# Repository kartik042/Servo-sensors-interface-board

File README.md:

This interface board uses Arduino board to control servo motors and has the following features:
1. Read data from airflow sensors
2. Uses 12VDC input
3. Has a TFT screen to display sensor values and UI elements to control the motors.
4. LDO voltage regulator MIC2940A to convert 12VDC to 3.3VDC
5. TMUX1208PWR multiplexer for data and clock signals
6. Pressure sensor that measures static pressure and the data is available on the display

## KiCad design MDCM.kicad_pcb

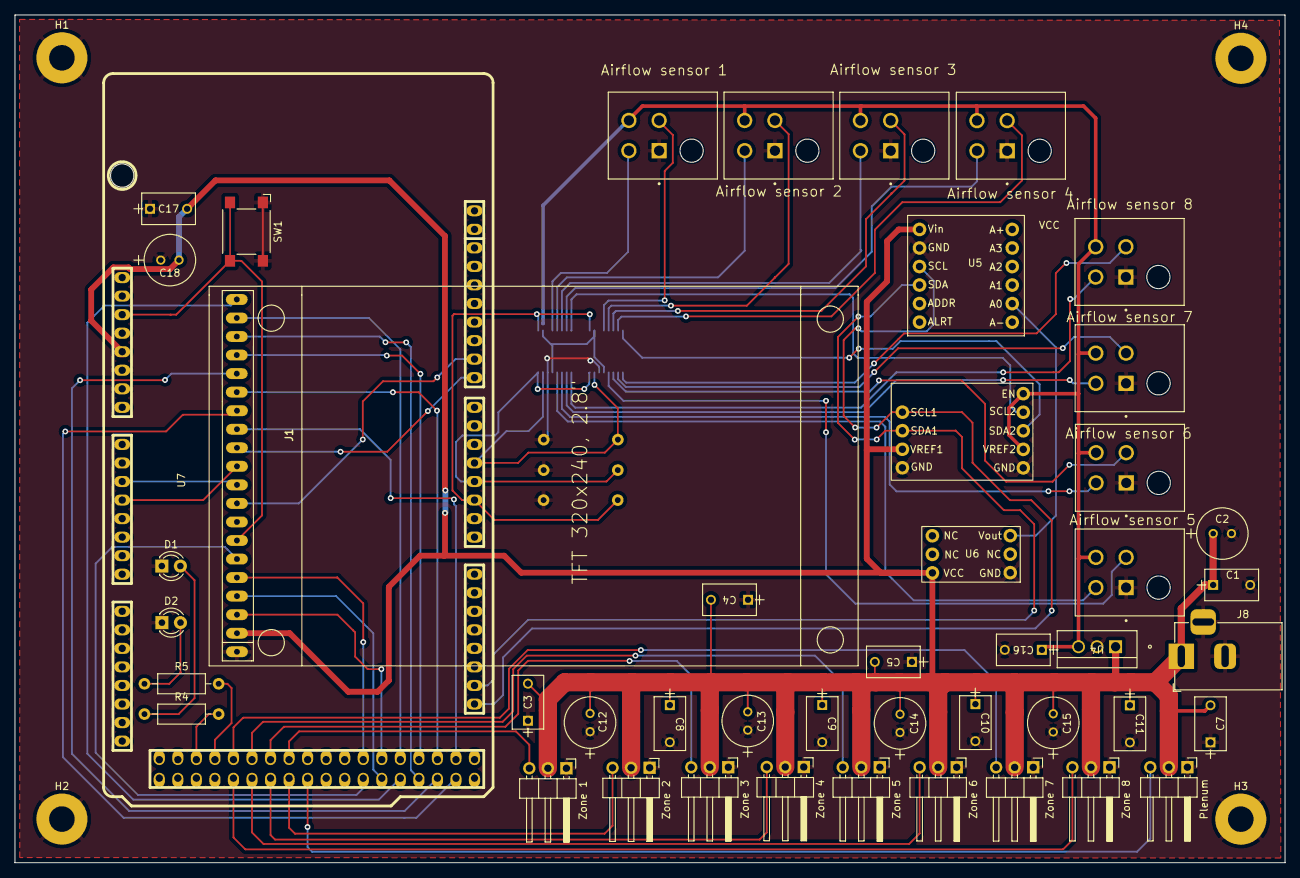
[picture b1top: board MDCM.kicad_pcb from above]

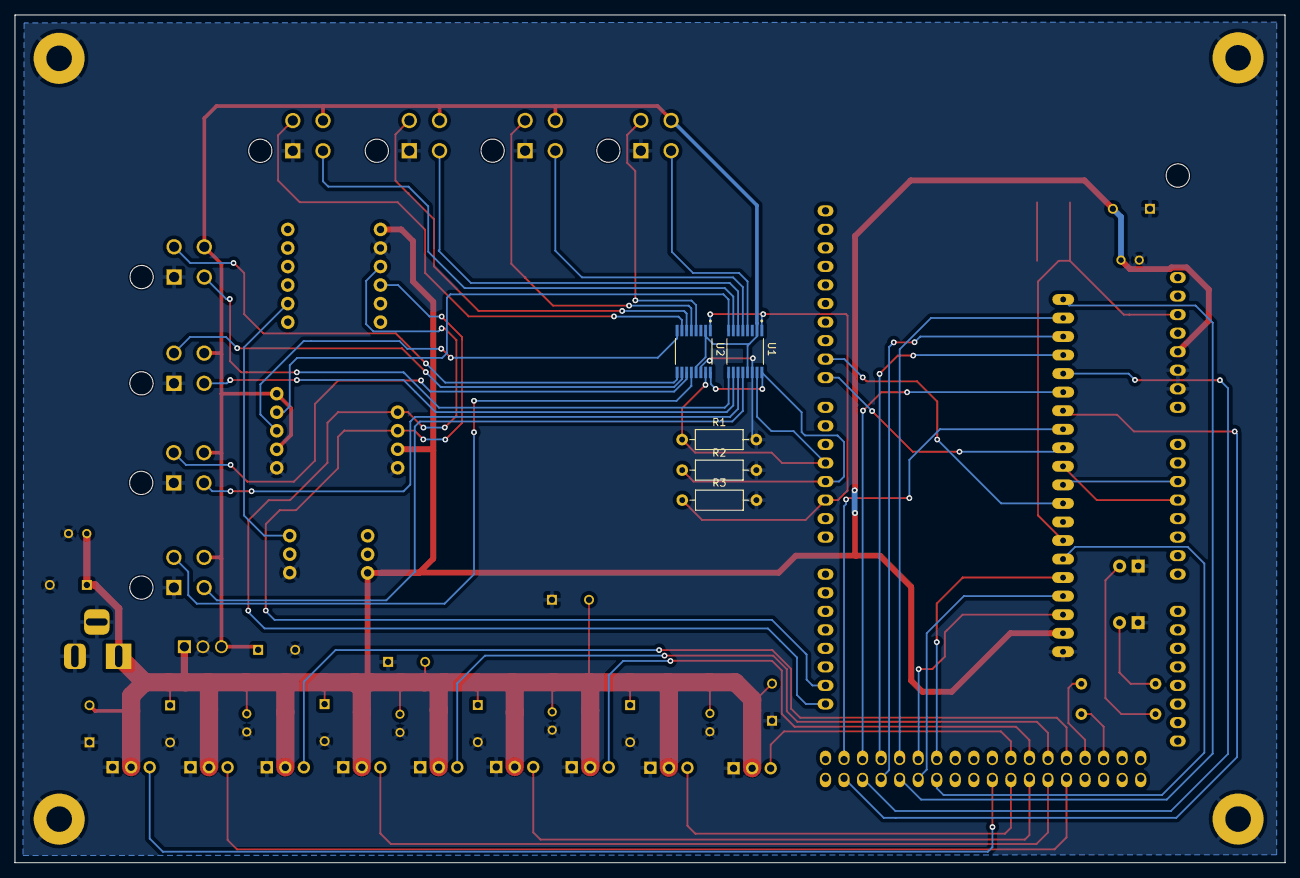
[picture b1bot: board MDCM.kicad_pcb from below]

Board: 2 copper layers, 174.0 x 116.1 mm, 55 parts (5 on the bottom side), 57 nets.

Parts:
Airflow sensor 1: J2; TE_1-770174-1
Airflow sensor 2: J3; TE_1-770174-1
Airflow sensor 3: J4; TE_1-770174-1
Airflow sensor 4: J5; TE_1-770174-1
Airflow sensor 5: J15; TE_1-770174-1
Airflow sensor 6: J16; TE_1-770174-1
Airflow sensor 7: J17; TE_1-770174-1
Airflow sensor 8: J18; TE_1-770174-1
C1, C16: 1uF; CAP_C330C_MR_X7R_KEM
C2, C12, C13, C14, C15, C18: 100uF; CAP_YX_6P3X11_RUB
C3, C4, C5, C7, C8, C9, C10, C11, C17: 0.1uF; CAP_C330C_MR_X7R_KEM
D1, D2: LED; LED_D3.0mm
H1, H2, H3, H4: MountingHole_Pad; MountingHole_3.5mm_Pad
J1: Arduino_Mega_Header; arduino_mega_header
J8: Barrel_Jack_Switch_Pin3Ring; BarrelJack_Horizontal
Plenum: Motor Connector 9; PinHeader_1x03_P2.54mm_Horizontal
R1, R2, R3: 10K; R_Axial_DIN0207_L6.3mm_D2.5mm_P10.16mm_Horizontal
R4, R5: R; R_Axial_DIN0207_L6.3mm_D2.5mm_P10.16mm_Horizontal
SW1: SW_Omron_B3FS; SW_SPST_Omron_B3FS-100xP
U1, U2: TMUX1208PWR; SOP65P640X120-16N
U3: Level Shifter
U4: MIC2940A-3.3WT; TO220-3LD-PL-1_MCH
U5: 12 Bit ADC_1
U6: Pressure Sensor
U7: TFT_320x240; TFT-320x240
Zone 1: Motor Connector 1; PinHeader_1x03_P2.54mm_Horizontal
Zone 2: Motor Connector 2; PinHeader_1x03_P2.54mm_Horizontal
Zone 3: Motor Connector 3; PinHeader_1x03_P2.54mm_Horizontal
Zone 4: Motor Connector 4; PinHeader_1x03_P2.54mm_Horizontal
Zone 5: Motor Connector 5; PinHeader_1x03_P2.54mm_Horizontal
Zone 6: Motor Connector 6; PinHeader_1x03_P2.54mm_Horizontal
Zone 7: Motor Connector 7; PinHeader_1x03_P2.54mm_Horizontal
Zone 8: Motor Connector 8; PinHeader_1x03_P2.54mm_Horizontal

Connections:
/3.3V: Airflow sensor 1.2, Airflow sensor 2.2, Airflow sensor 3.2, Airflow sensor 4.2, Airflow sensor 5.2, Airflow sensor 6.2, Airflow sensor 7.2, Airflow sensor 8.2, C16.1, U1.2 (EN), U1.13 (VDD), U2.2 (EN), U2.13 (VDD), U3.6 (VREF2), U3.9 (EN), U4.3 (OUTPUT)
/SCL_1: Airflow sensor 1.4, U1.4 (S1)
/SCL_2: Airflow sensor 2.4, U1.5 (S2)
/SCL_3: Airflow sensor 3.4, U1.6 (S3)
/SCL_4: Airflow sensor 4.4, U1.7 (S4)
/SCL_5: Airflow sensor 5.4, U1.12 (S5)
/SCL_6: Airflow sensor 6.4, U1.11 (S6)
/SCL_7: Airflow sensor 7.4, U1.10 (S7)
/SCL_8: Airflow sensor 8.4, U1.9 (S8)
/SDA_1: Airflow sensor 1.3, U2.4 (S1)
/SDA_2: Airflow sensor 2.3, U2.5 (S2)
/SDA_3: Airflow sensor 3.3, U2.6 (S3)
/SDA_4: Airflow sensor 4.3, U2.7 (S4)
/SDA_5: Airflow sensor 5.3, U2.12 (S5)
/SDA_6: Airflow sensor 6.3, U2.11 (S6)
/SDA_7: Airflow sensor 7.3, U2.10 (S7)
/SDA_8: Airflow sensor 8.3, U2.9 (S8)
GND: Airflow sensor 1.1, Airflow sensor 2.1, Airflow sensor 3.1, Airflow sensor 4.1, Airflow sensor 5.1, Airflow sensor 6.1, Airflow sensor 7.1, Airflow sensor 8.1, C1.2, C2.2, C3.1, C4.1, C5.1, C7.1, C8.2, C9.2, C10.2, C11.2, C12.1, C13.1, C14.1, C15.1, C16.2, C17.1, C18.1, D1.1 (K), D2.1 (K), H1.1, H2.1, H3.1, H4.1, J1.6 (GND), J1.7 (GND), J8.2, J8.3, Plenum.1, R1.2, R2.2, R3.2, SW1.1, U1.14 (GND), U2.14 (GND), U3.4 (GND), U3.5 (GND), U4.2 (GROUND), U5.2 (GND), U6.1 (GND), U7.1 (GND), Zone 1.1, Zone 2.1, Zone 3.1, Zone 4.1, Zone 5.1, Zone 6.1, Zone 7.1, Zone 8.1
unnamed: D1.2 (A), R4.1
unnamed: D2.2 (A), R5.1
unnamed: J1.11 (AD2), U7.10 (Y+)
unnamed: J1.12 (AD3), U7.11 (X-)
unnamed: J1.41 (PIN22), U7.13 (D0)
unnamed: J1.59 (PIN23), U7.14 (D1)
unnamed: J1.40 (PIN24), U7.15 (D2)
unnamed: J1.58 (PIN25), U7.16 (D3)
unnamed: J1.39 (PIN26), U7.17 (D4)
unnamed: J1.57 (PIN27), U7.18 (D5)
unnamed: J1.38 (PIN28), U7.19 (D6)
unnamed: J1.56 (PIN29), U7.20 (D7)
unnamed: J1.37 (PIN30), U7.3 (CS)
unnamed: J1.55 (PIN31), U7.4 (C/D)
unnamed: J1.36 (PIN32), U7.5 (WR)
unnamed: J1.54 (PIN33), U7.6 (RD)
unnamed: J1.51 (PIN39), Plenum.3
unnamed: J1.32 (PIN40), Zone 1.3
unnamed: J1.50 (PIN41), Zone 2.3
unnamed: J1.31 (PIN42), Zone 3.3
unnamed: J1.49 (PIN43), Zone 4.3
unnamed: J1.30 (PIN44), Zone 5.3
unnamed: J1.48 (PIN45), Zone 6.3
unnamed: J1.29 (PIN46), Zone 7.3
unnamed: J1.47 (PIN47), Zone 8.3
unnamed: J1.28 (PIN48), R5.2
unnamed: J1.27 (PIN50), R4.2
unnamed: J1.71 (PWM2/2), R3.1, U1.1 (A0), U2.1 (A0)
unnamed: J1.72 (PWM3/3), R2.1, U1.16 (A1), U2.16 (A1)
unnamed: J1.77 (PWM8/8), U7.12 (Y-)
unnamed: J1.78 (PWM9/9), U7.9 (X+)
unnamed: J1.3 (RESET), SW1.2, U7.7 (RST)
unnamed: J1.61 (SCL0-3/TWCK1/21), U3.1 (SCL1), U5.3 (SCL)
unnamed: J1.62 (SDA0-3/TWD1/20), U3.2 (SDA1), U5.4 (SDA)
unnamed: J1.73 (SS1/PWM4/SD-CS/4), R1.1, U1.15 (A2), U2.15 (A2)
unnamed: U1.8 (D), U3.8 (SCL2)
unnamed: U2.8 (D), U3.7 (SDA2)
unnamed: U5.8 (A0), U6.3 (Vout)
VCC: C1.1, C2.1, C3.2, C4.2, C5.2, C7.2, C8.1, C9.1, C10.1, C11.1, C12.2, C13.2, C14.2, C15.2, C17.2, C18.2, J1.5 (5V), J8.1, Plenum.2, U3.3 (VREF1), U4.1 (INPUT), U5.1 (Vin), U6.6 (VCC), U7.2 (Vin), Zone 1.2, Zone 2.2, Zone 3.2, Zone 4.2, Zone 5.2, Zone 6.2, Zone 7.2, Zone 8.2
